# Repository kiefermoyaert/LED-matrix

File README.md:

# LED-matrix
I am creating a LED matrix, existing of a 7x7 grid of WS2812B adressable RGB LED's. The board does have WiFi and bluetooth capablities.

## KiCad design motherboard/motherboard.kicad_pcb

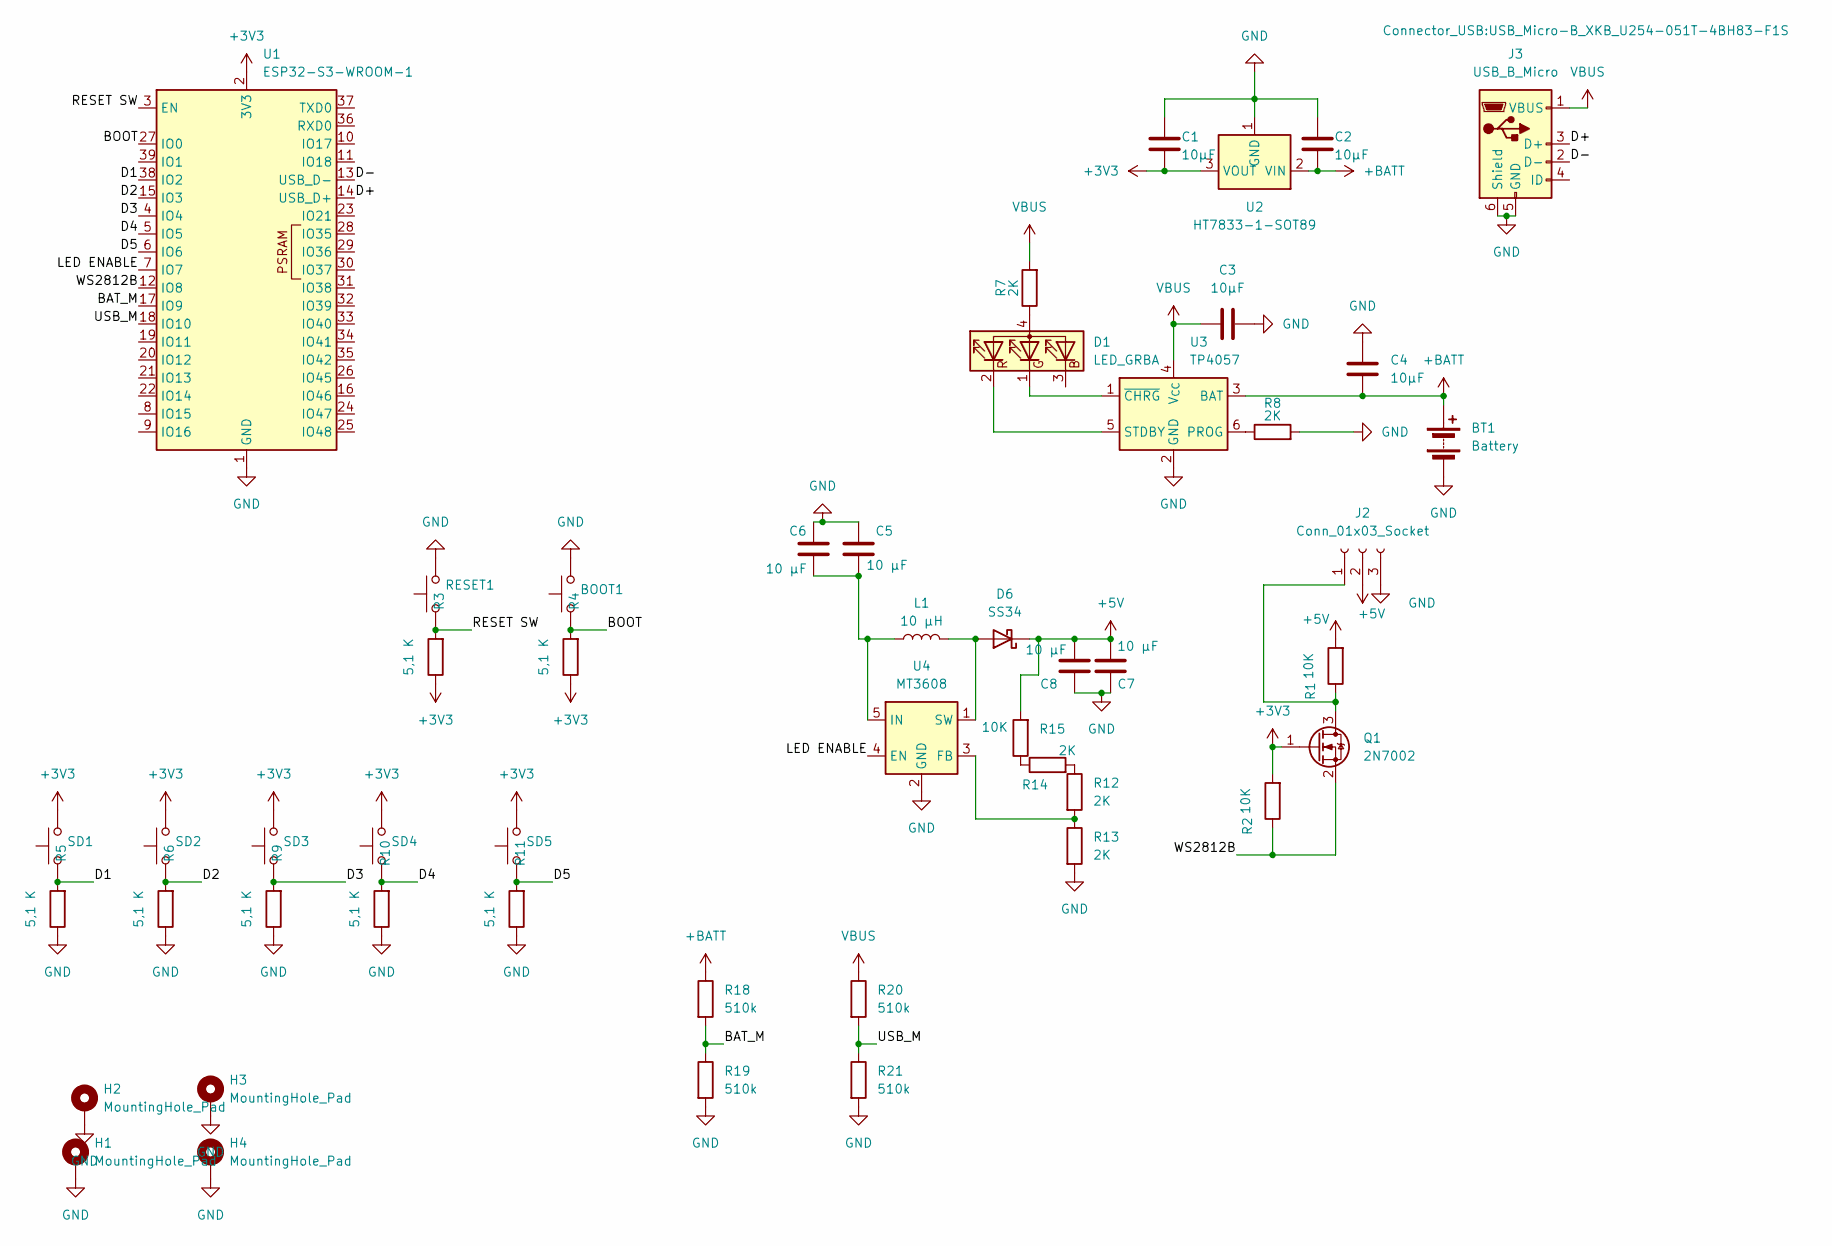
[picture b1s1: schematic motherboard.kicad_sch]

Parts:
BOOT1: SW_PUSH_6mm
BT1: Battery; BatteryHolder_Keystone_1042_1x18650
C1, C2, C3, C4: 10μF; C_1206_3216Metric
C5, C6, C7, C8: 10 µF; C_1206_3216Metric
D1: LED_GRBA; LED_Cree-PLCC4_3.2x2.8mm_CCW
D6: SS34; D_SMA
H1, H2, H3, H4: MountingHole_Pad; MountingHole_3.2mm_M3_ISO7380_Pad
J2: Conn_01x03_Socket; JST_XH_B3B-XH-A_1x03_P2.50mm_Vertical
J3: USB_B_Micro; USB_Micro-B_XKB_U254-051T-4BH83-F1S
L1: 10 µH; L_12x12mm_H8mm
Q1: 2N7002; SOT-23
R1, R2, R15: 10K; R_0805_2012Metric
R3, R4, R5, R6, R9, R10, R11: 5,1 K; R_0805_2012Metric
R7, R8, R12, R13, R14: 2K; R_0805_2012Metric
R18, R19, R20, R21: 510k; R_1206_3216Metric
RESET1: SW_PUSH_6mm
SD1, SD2, SD3, SD4, SD5: SW_PUSH_6mm
U1: ESP32-S3-WROOM-1
U2: HT7833-1-SOT89; SOT-89-3_Handsoldering
U3: TP4057; SOT-23-6
U4: MT3608; SOT-23-6

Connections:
+3V3: C1.2, Q1.1 (G), R2.2, R3.1, R4.1, SD1.2, SD2.2, SD3.2, SD4.2, SD5.2, U1.2 (3V3), U2.3 (VOUT)
+5V: C7.1, C8.1, D6.1 (K), J2.2, R1.2, R15.2
+BATT: BT1.1 (+), C2.2, C4.2, R18.1, U2.2 (VIN), U3.3 (BAT)
/BAT_M: R18.2, R19.1, U1.17 (IO9)
/BOOT: BOOT1.1, R4.2, U1.27 (IO0)
/D1: R5.2, SD1.1, U1.38 (IO2)
/D2: R6.2, SD2.1, U1.15 (IO3)
/D3: R9.2, SD3.1, U1.4 (IO4)
/D4: R10.2, SD4.1, U1.5 (IO5)
/D5: R11.2, SD5.1, U1.6 (IO6)
/D+: J3.3 (D+), U1.14 (USB_D+)
/D-: J3.2 (D-), U1.13 (USB_D-)
/LED ENABLE: U1.7 (IO7), U4.4 (EN)
/RESET SW: R3.2, RESET1.1, U1.3 (EN)
/USB_M: R20.2, R21.1, U1.18 (IO10)
/WS2812B: Q1.2 (S), R2.1, U1.12 (IO8)
GND: BOOT1.2, BT1.2 (-), C1.1, C2.1, C3.2, C4.1, C5.2, C6.2, C7.2, C8.2, H1.1, H2.1, H3.1, H4.1, J2.3, J3.5 (GND), J3.6 (Shield), R5.1, R6.1, R8.2, R9.1, R10.1, R11.1, R13.2, R19.2, R21.2, RESET1.2, U1.1 (GND), U1.40 (GND), U1.41 (GND), U2.1 (GND), U3.2 (GND), U4.2 (GND)
unnamed: D1.4 (A), R7.1
unnamed: D1.1 (GK), U3.1 (~CHRG)
unnamed: D1.2 (RK), U3.5 (STDBY)
unnamed: D6.2 (A), L1.2, U4.1 (SW)
unnamed: J2.1, Q1.3 (D), R1.1
unnamed: R12.1, R14.2
unnamed: R14.1, R15.1
unnamed: R8.1, U3.6 (PROG)
unnamed: R12.2, R13.1, U4.3 (FB)
unnamed: C5.1, C6.1, L1.1, U4.5 (IN)
VBUS: C3.1, J3.1 (VBUS), R7.2, R20.1, U3.4 (V_{CC})

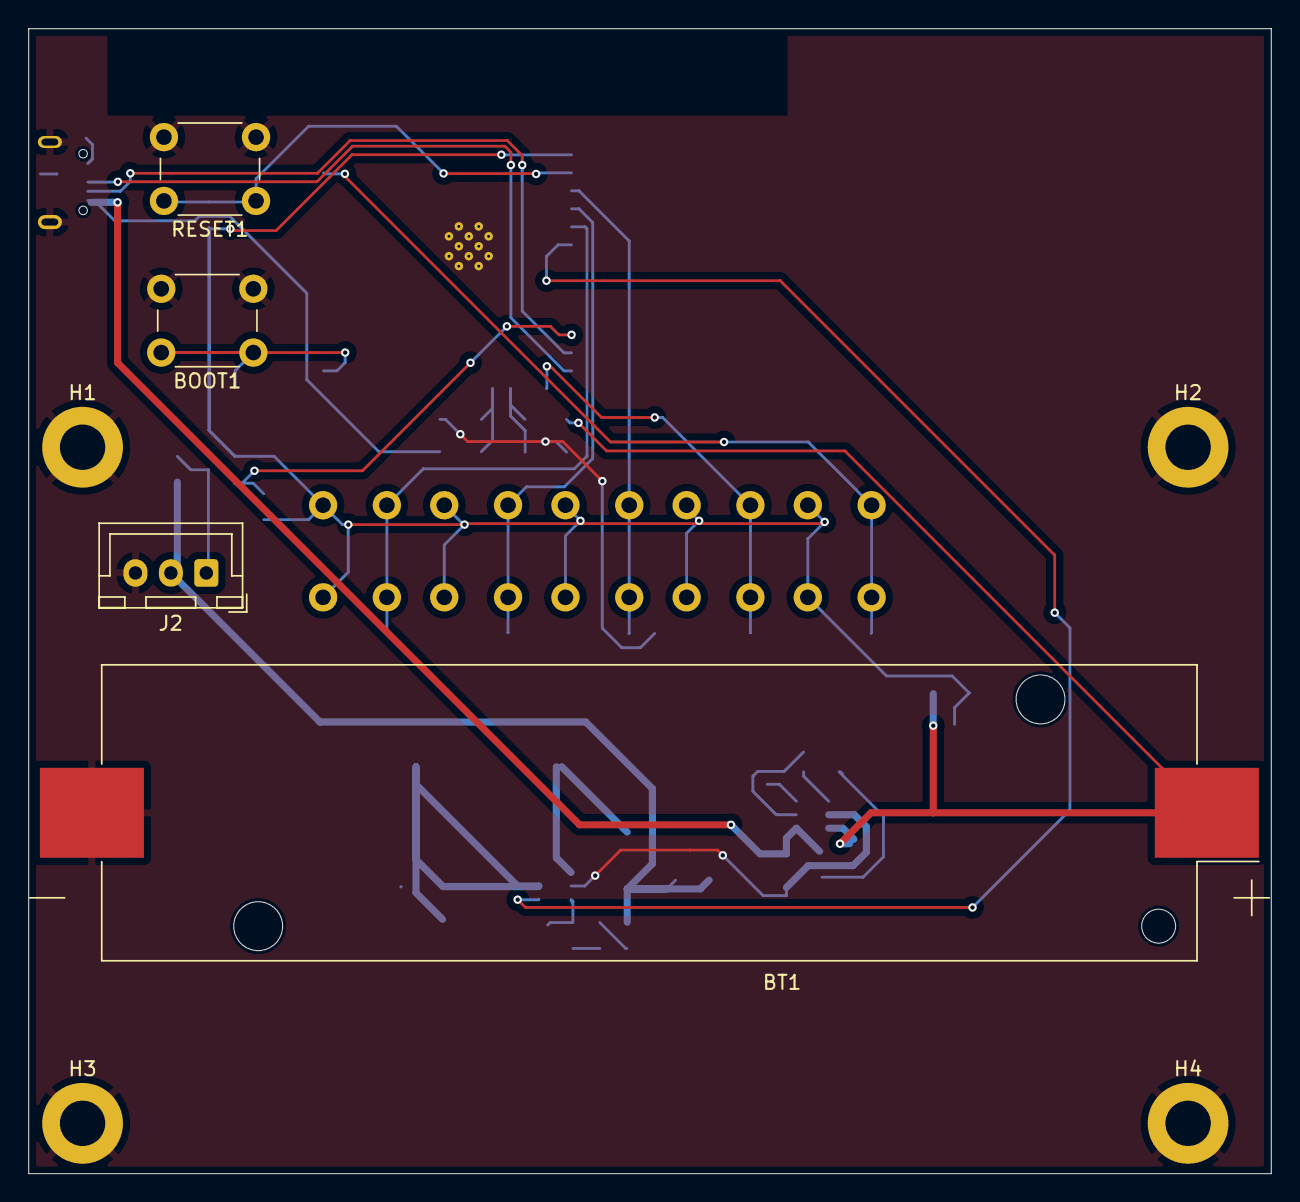
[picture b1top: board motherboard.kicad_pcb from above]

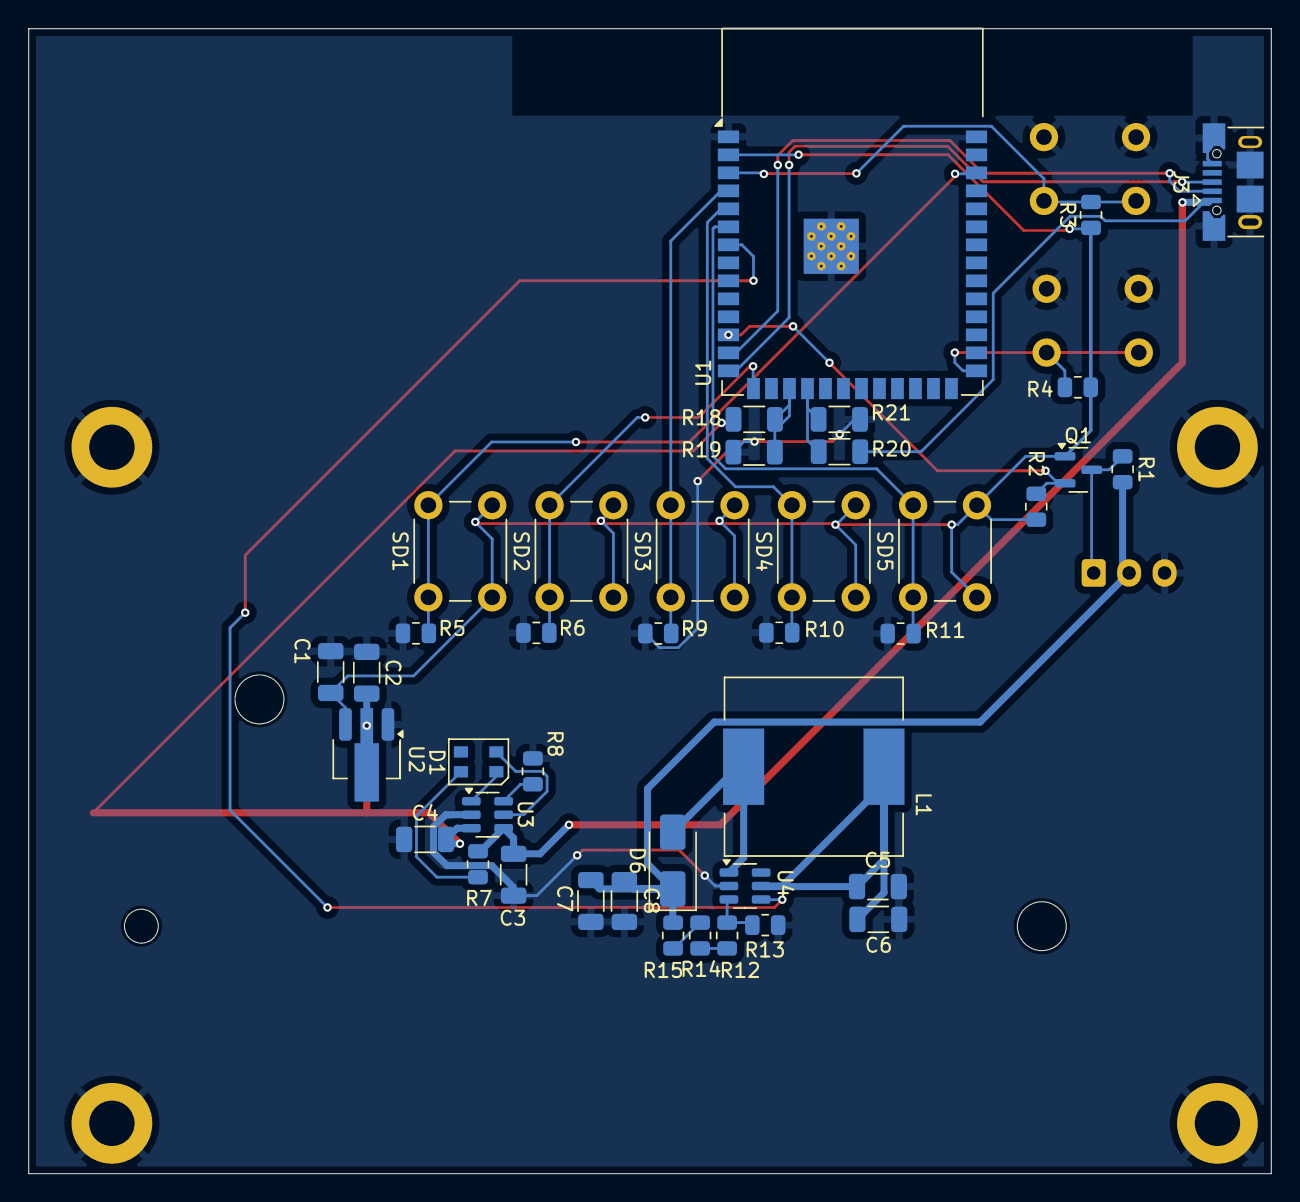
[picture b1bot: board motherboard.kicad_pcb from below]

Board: 2 copper layers, 87.7 x 80.8 mm, 49 parts (41 on the bottom side), 28 nets.

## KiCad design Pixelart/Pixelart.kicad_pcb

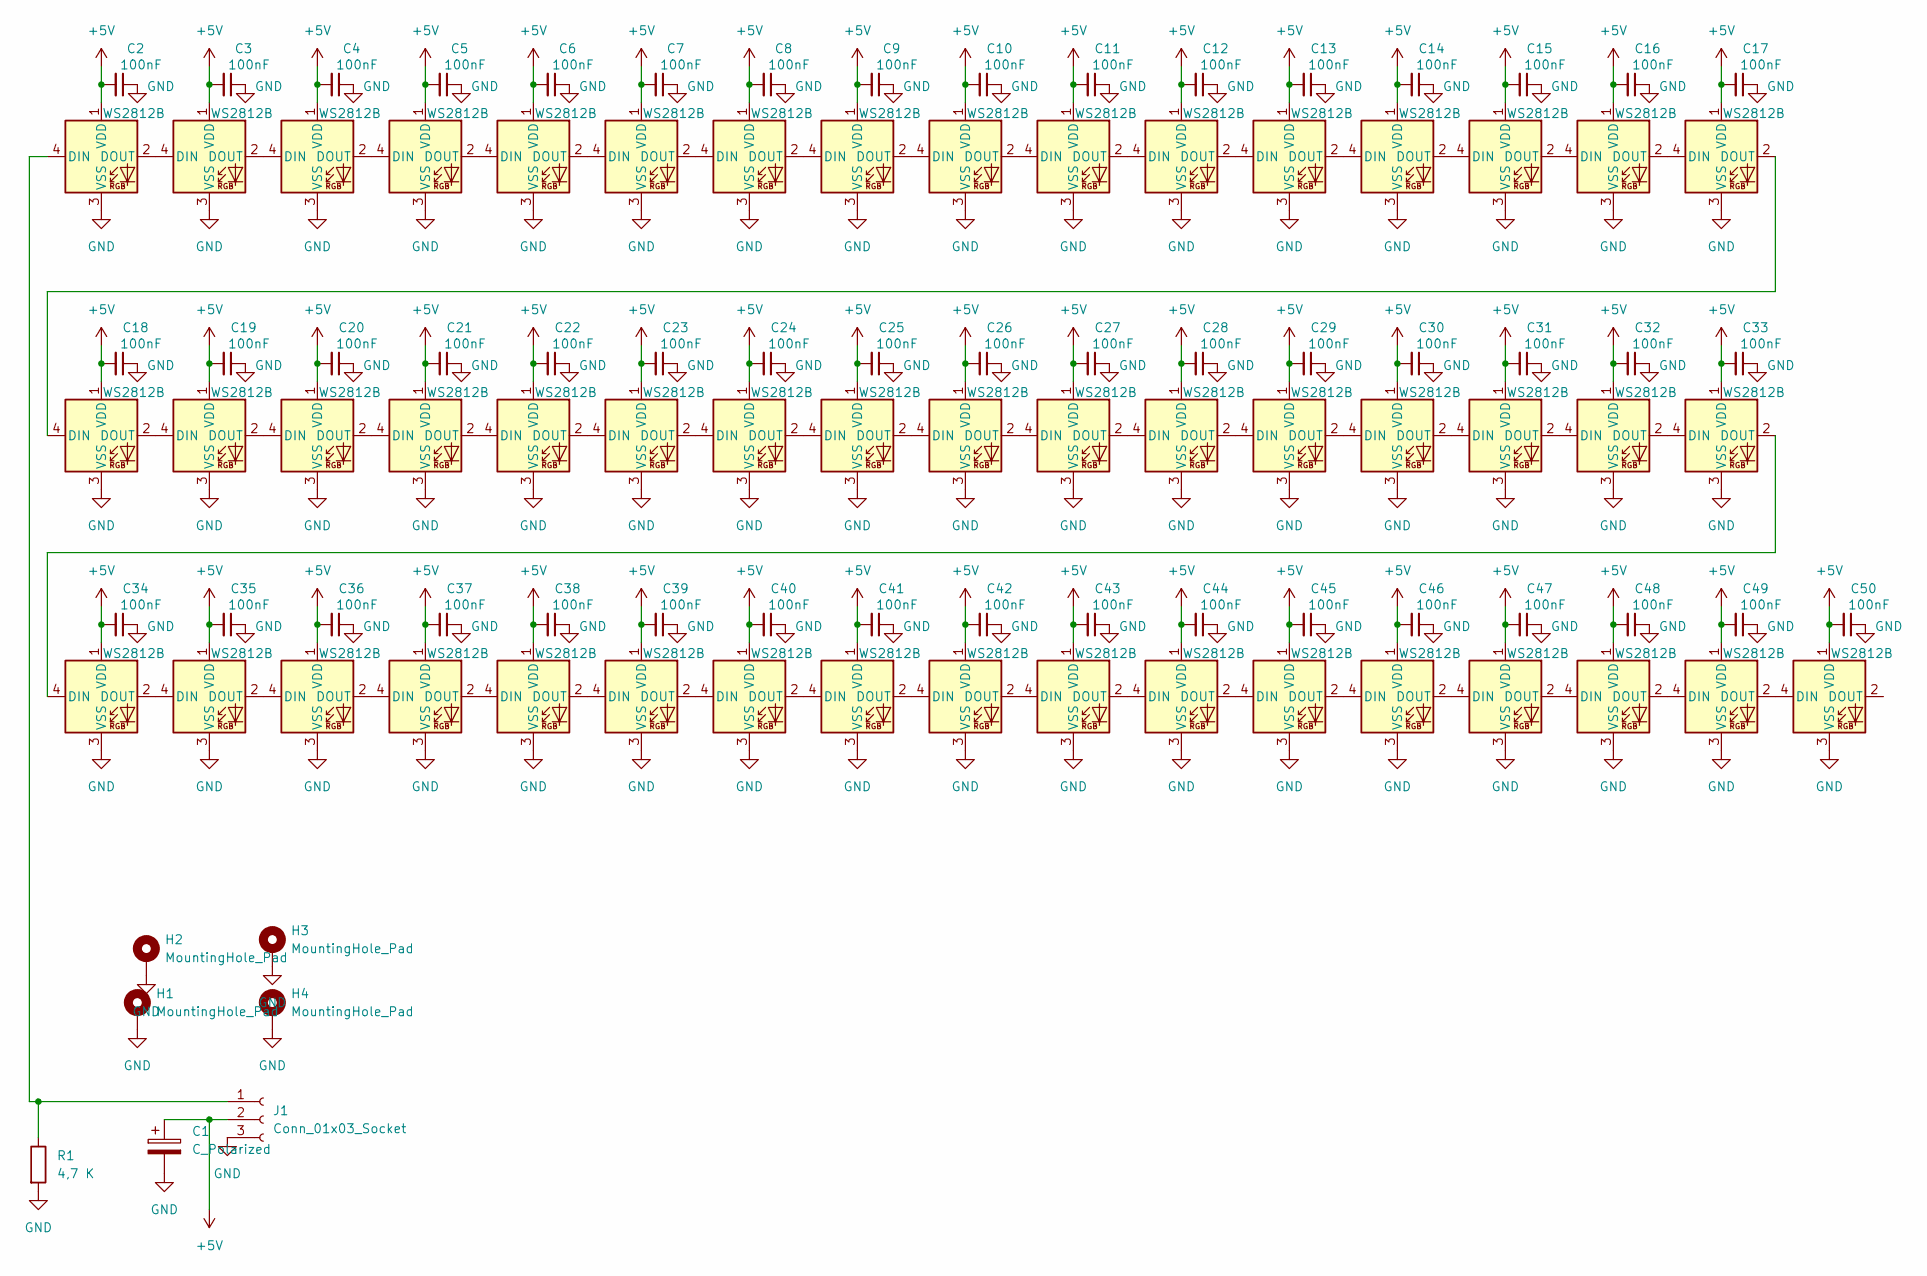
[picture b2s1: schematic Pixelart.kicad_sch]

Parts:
C1: C_Polarized; CP_Radial_D5.0mm_P2.00mm
C2, C3, C4, C5, C6, C7, C8, C9, C10, C11, C12, C13, C14, C15, C16, C17, C18, C19, C20, C21, C22, C23, C24, C25, C26, C27, C28, C29, C30, C31, C32, C33, C34, C35, C36, C37, C38, C39, C40, C41, C42, C43, C44, C45, C46, C47, C48, C49, C50: 100nF; C_0805_2012Metric
D1, D2, D3, D4, D5, D6, D7, D8, D9, D10, D11, D12, D13, D14, D15, D16, D17, D18, D19, D20, D21, D22, D23, D24, D25, D26, D27, D28, D29, D30, D31, D32, D33, D34, D35, D36, D37, D38, D39, D40, D41, D42, D43, D44, D45, D46, D47, D48, D49: WS2812B; LED_WS2812B_PLCC4_5.0x5.0mm_P3.2mm
H1, H2, H3, H4: MountingHole_Pad; MountingHole_3.2mm_M3_ISO7380_Pad
J1: Conn_01x03_Socket; JST_XH_B3B-XH-A_1x03_P2.50mm_Vertical
R1: 4,7 K; R_0805_2012Metric

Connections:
+5V: C1.1, C2.2, C3.2, C4.2, C5.2, C6.2, C7.2, C8.2, C9.2, C10.2, C11.2, C12.2, C13.2, C14.2, C15.2, C16.2, C17.2, C18.2, C19.2, C20.2, C21.2, C22.2, C23.2, C24.2, C25.2, C26.2, C27.2, C28.2, C29.2, C30.2, C31.2, C32.2, C33.2, C34.2, C35.2, C36.2, C37.2, C38.2, C39.2, C40.2, C41.2, C42.2, C43.2, C44.2, C45.2, C46.2, C47.2, C48.2, C49.2, C50.2, D1.1 (VDD), D2.1 (VDD), D3.1 (VDD), D4.1 (VDD), D5.1 (VDD), D6.1 (VDD), D7.1 (VDD), D8.1 (VDD), D9.1 (VDD), D10.1 (VDD), D11.1 (VDD), D12.1 (VDD), D13.1 (VDD), D14.1 (VDD), D15.1 (VDD), D16.1 (VDD), D17.1 (VDD), D18.1 (VDD), D19.1 (VDD), D20.1 (VDD), D21.1 (VDD), D22.1 (VDD), D23.1 (VDD), D24.1 (VDD), D25.1 (VDD), D26.1 (VDD), D27.1 (VDD), D28.1 (VDD), D29.1 (VDD), D30.1 (VDD), D31.1 (VDD), D32.1 (VDD), D33.1 (VDD), D34.1 (VDD), D35.1 (VDD), D36.1 (VDD), D37.1 (VDD), D38.1 (VDD), D39.1 (VDD), D40.1 (VDD), D41.1 (VDD), D42.1 (VDD), D43.1 (VDD), D44.1 (VDD), D45.1 (VDD), D46.1 (VDD), D47.1 (VDD), D48.1 (VDD), D49.1 (VDD), J1.2
GND: C1.2, C2.1, C3.1, C4.1, C5.1, C6.1, C7.1, C8.1, C9.1, C10.1, C11.1, C12.1, C13.1, C14.1, C15.1, C16.1, C17.1, C18.1, C19.1, C20.1, C21.1, C22.1, C23.1, C24.1, C25.1, C26.1, C27.1, C28.1, C29.1, C30.1, C31.1, C32.1, C33.1, C34.1, C35.1, C36.1, C37.1, C38.1, C39.1, C40.1, C41.1, C42.1, C43.1, C44.1, C45.1, C46.1, C47.1, C48.1, C49.1, C50.1, D1.3 (VSS), D2.3 (VSS), D3.3 (VSS), D4.3 (VSS), D5.3 (VSS), D6.3 (VSS), D7.3 (VSS), D8.3 (VSS), D9.3 (VSS), D10.3 (VSS), D11.3 (VSS), D12.3 (VSS), D13.3 (VSS), D14.3 (VSS), D15.3 (VSS), D16.3 (VSS), D17.3 (VSS), D18.3 (VSS), D19.3 (VSS), D20.3 (VSS), D21.3 (VSS), D22.3 (VSS), D23.3 (VSS), D24.3 (VSS), D25.3 (VSS), D26.3 (VSS), D27.3 (VSS), D28.3 (VSS), D29.3 (VSS), D30.3 (VSS), D31.3 (VSS), D32.3 (VSS), D33.3 (VSS), D34.3 (VSS), D35.3 (VSS), D36.3 (VSS), D37.3 (VSS), D38.3 (VSS), D39.3 (VSS), D40.3 (VSS), D41.3 (VSS), D42.3 (VSS), D43.3 (VSS), D44.3 (VSS), D45.3 (VSS), D46.3 (VSS), D47.3 (VSS), D48.3 (VSS), D49.3 (VSS), H1.1, H2.1, H3.1, H4.1, J1.3, R1.2
unnamed: D1.4 (DIN), J1.1, R1.1
unnamed: D1.2 (DOUT), D2.4 (DIN)
unnamed: D2.2 (DOUT), D3.4 (DIN)
unnamed: D3.2 (DOUT), D4.4 (DIN)
unnamed: D4.2 (DOUT), D5.4 (DIN)
unnamed: D5.2 (DOUT), D6.4 (DIN)
unnamed: D6.2 (DOUT), D7.4 (DIN)
unnamed: D7.2 (DOUT), D8.4 (DIN)
unnamed: D8.2 (DOUT), D9.4 (DIN)
unnamed: D9.2 (DOUT), D10.4 (DIN)
unnamed: D10.2 (DOUT), D11.4 (DIN)
unnamed: D11.2 (DOUT), D12.4 (DIN)
unnamed: D12.2 (DOUT), D13.4 (DIN)
unnamed: D13.2 (DOUT), D14.4 (DIN)
unnamed: D14.2 (DOUT), D15.4 (DIN)
unnamed: D15.2 (DOUT), D16.4 (DIN)
unnamed: D16.2 (DOUT), D17.4 (DIN)
unnamed: D17.2 (DOUT), D18.4 (DIN)
unnamed: D18.2 (DOUT), D19.4 (DIN)
unnamed: D19.2 (DOUT), D20.4 (DIN)
unnamed: D20.2 (DOUT), D21.4 (DIN)
unnamed: D21.2 (DOUT), D22.4 (DIN)
unnamed: D22.2 (DOUT), D23.4 (DIN)
unnamed: D23.2 (DOUT), D24.4 (DIN)
unnamed: D24.2 (DOUT), D25.4 (DIN)
unnamed: D25.2 (DOUT), D26.4 (DIN)
unnamed: D26.2 (DOUT), D27.4 (DIN)
unnamed: D27.2 (DOUT), D28.4 (DIN)
unnamed: D28.2 (DOUT), D29.4 (DIN)
unnamed: D29.2 (DOUT), D30.4 (DIN)
unnamed: D30.2 (DOUT), D31.4 (DIN)
unnamed: D31.2 (DOUT), D32.4 (DIN)
unnamed: D32.2 (DOUT), D33.4 (DIN)
unnamed: D33.2 (DOUT), D34.4 (DIN)
unnamed: D34.2 (DOUT), D35.4 (DIN)
unnamed: D35.2 (DOUT), D36.4 (DIN)
unnamed: D36.2 (DOUT), D37.4 (DIN)
unnamed: D37.2 (DOUT), D38.4 (DIN)
unnamed: D38.2 (DOUT), D39.4 (DIN)
unnamed: D39.2 (DOUT), D40.4 (DIN)
unnamed: D40.2 (DOUT), D41.4 (DIN)
unnamed: D41.2 (DOUT), D42.4 (DIN)
unnamed: D42.2 (DOUT), D43.4 (DIN)
unnamed: D43.2 (DOUT), D44.4 (DIN)
unnamed: D44.2 (DOUT), D45.4 (DIN)
unnamed: D45.2 (DOUT), D46.4 (DIN)
unnamed: D46.2 (DOUT), D47.4 (DIN)
unnamed: D47.2 (DOUT), D48.4 (DIN)
unnamed: D48.2 (DOUT), D49.4 (DIN)

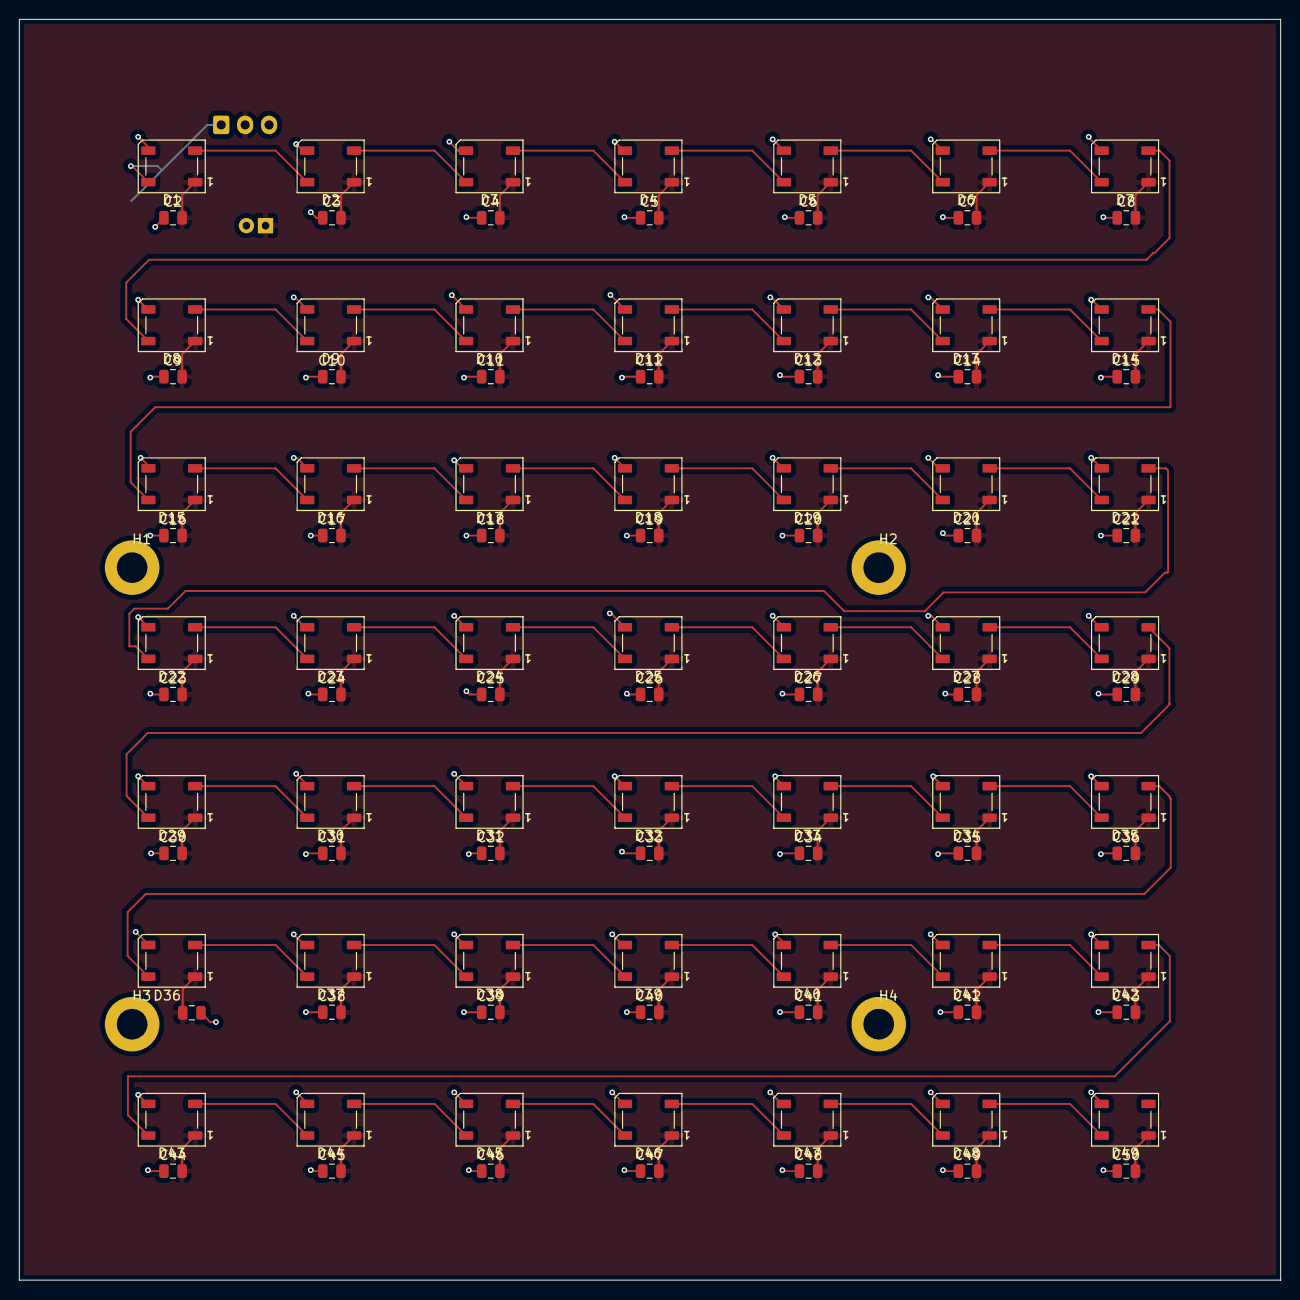
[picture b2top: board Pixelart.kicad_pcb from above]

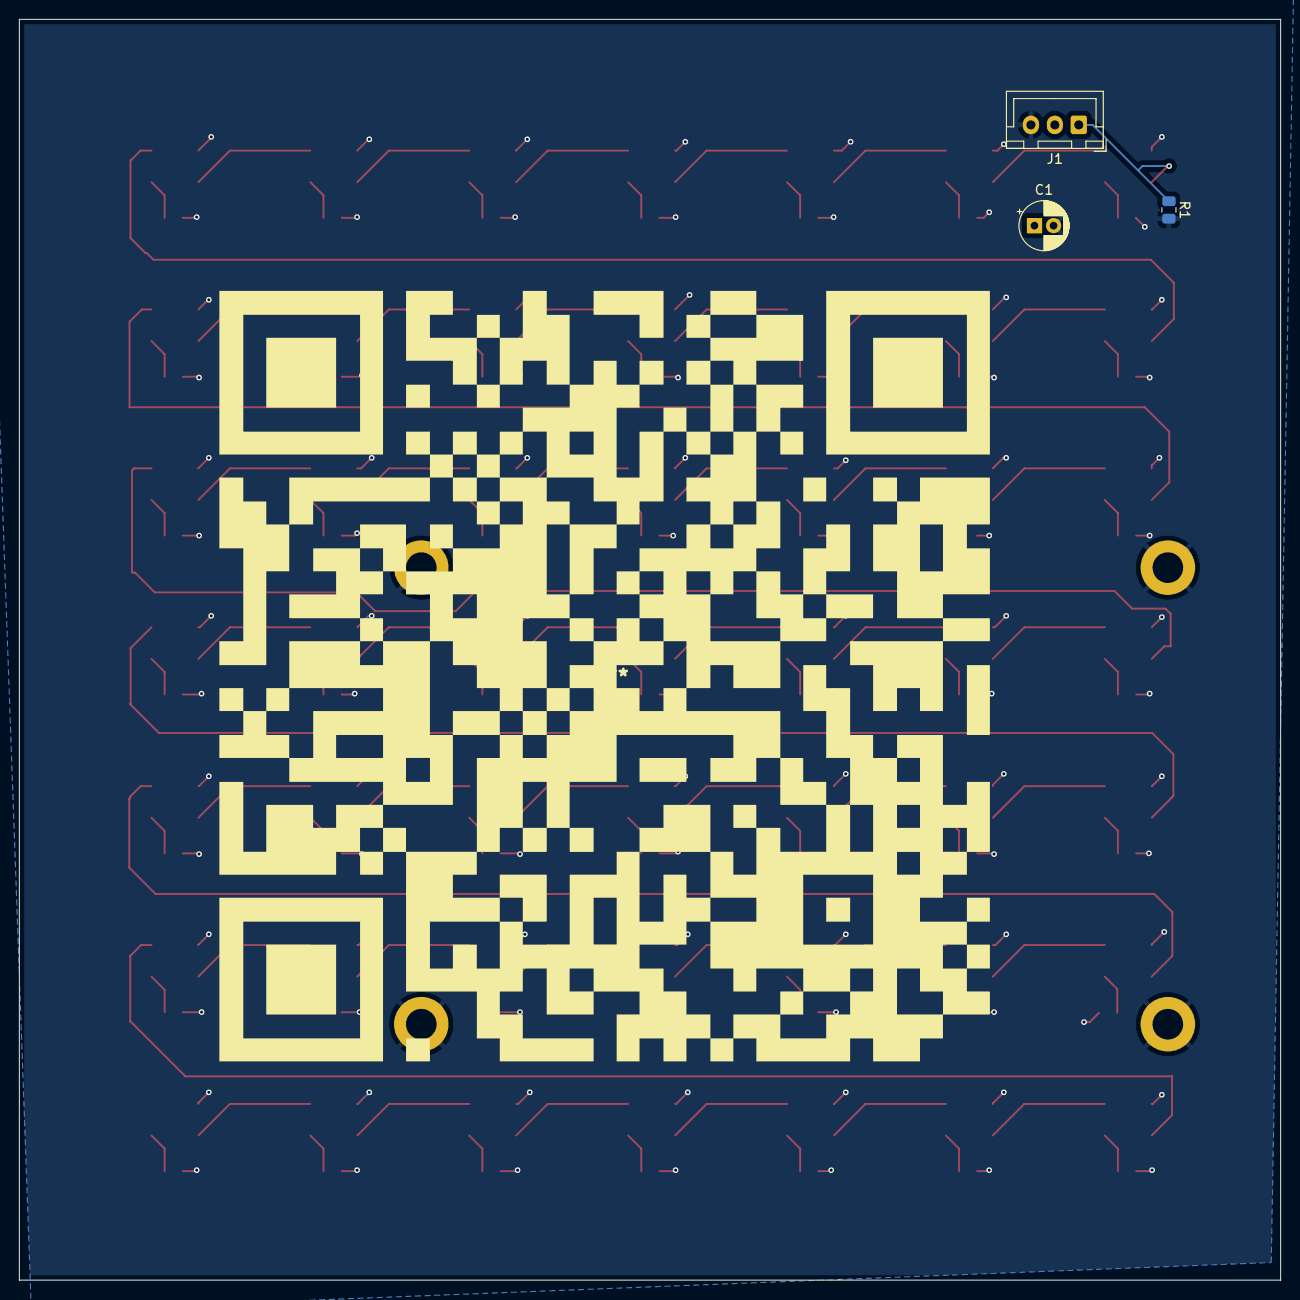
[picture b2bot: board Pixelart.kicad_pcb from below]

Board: 2 copper layers, 131.8 x 131.7 mm, 105 parts (3 on the bottom side), 51 nets.

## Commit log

2026-03-01 The PCB files - No code was written
